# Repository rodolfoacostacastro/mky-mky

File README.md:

# A mky-mky clone for an RP2040 custom board

## Arduino Code

updated code after first workshop with minor improvements and better comments :)! 

This the code is situable for a makey makey that works with the chip RP2040.

To upload with the Arduino IDE, you will need to use this board definition(!):

https://github.com/earlephilhower/arduino-pico/releases/download/global/package_rp2040_index.json

go here --> Arduino >settings and scroll down until "Additional boards manager URLs" and paste the link above.

When selecting your board, asure you that it is the Raspberryi Pico/RP definition (and not the native from Arduino)

The code's been modified and works with the educational breakout-board created by Rodolfo Acosta Castro 
for the workshop "Into the Circuit" @ HfS, Berlin. October 2024

Credits:

 //////// MaKey MaKey FIRMWARE v1.4 /////////////
 by: Eric Rosenbaum, Jay Silver, and Jim Lindblom
 MIT Media Lab & Sparkfun
 release: 7/5/2012

## KiCad Files 

you find in this repository the KiCad Project files of the RP2040 Board and the Keyboard extension.
They were created using KiCad 8.0

## Fabrication Files

if you want to order the pcbs yourself you find all the needed files here

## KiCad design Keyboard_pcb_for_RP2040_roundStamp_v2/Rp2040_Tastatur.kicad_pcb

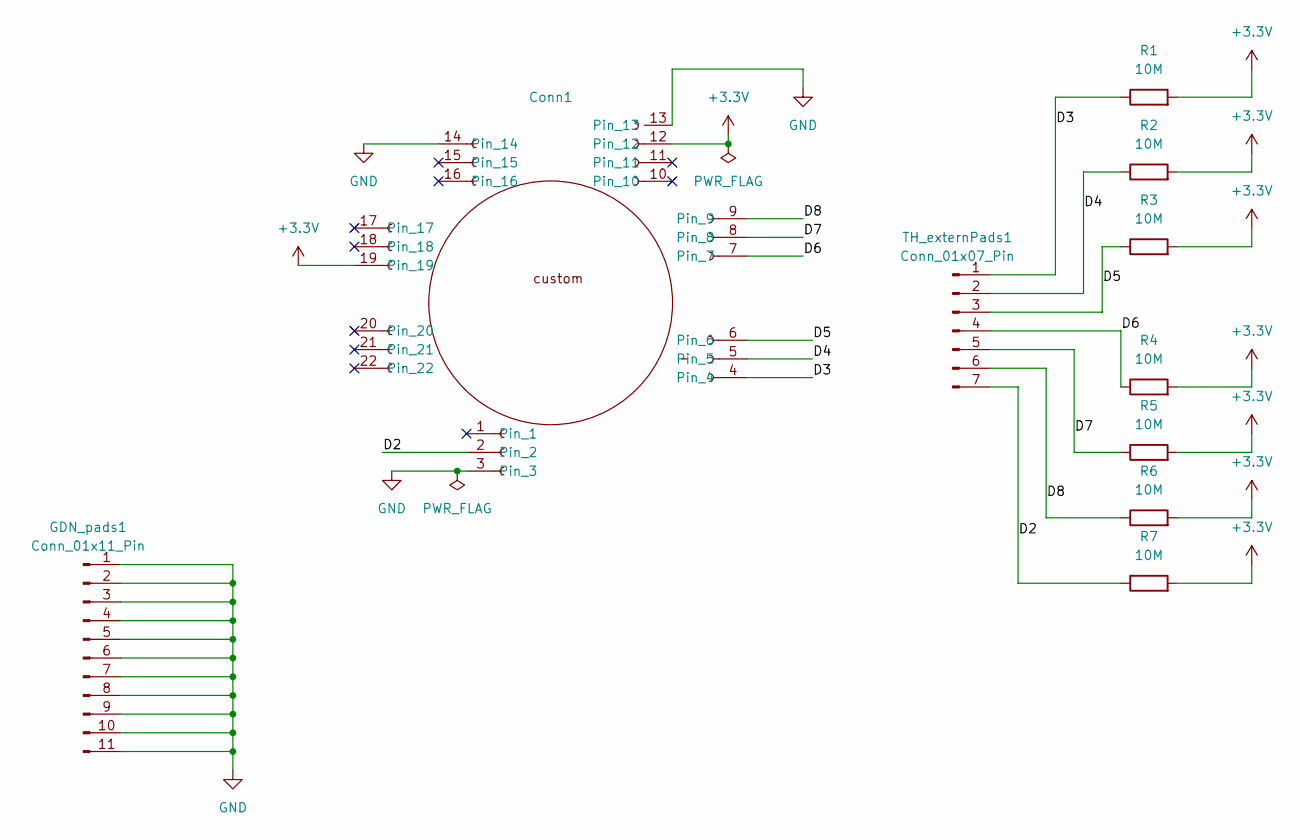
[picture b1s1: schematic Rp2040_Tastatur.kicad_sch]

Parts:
Conn1: mky_mky_boardPads
GDN_pads1: Conn_01x11_Pin; mky_mky_complete_GND
R1, R2, R3, R4, R5, R6, R7: 10M; R_0402_1005Metric_Pad0.72x0.64mm_HandSolder
TH_externPads1: Conn_01x07_Pin; mky_mky_externPads

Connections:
+3.3V: Conn1.12, Conn1.19, R1.2, R2.2, R3.2, R4.2, R5.2, R6.2, R7.2
/D2: Conn1.2, R7.1, TH_externPads1.7
/D3: Conn1.4, R1.1, TH_externPads1.1
/D4: Conn1.5, R2.1, TH_externPads1.2
/D5: Conn1.6, R3.1, TH_externPads1.3
/D6: Conn1.7, R4.1, TH_externPads1.4
/D7: Conn1.8, R5.1, TH_externPads1.5
/D8: Conn1.9, R6.1, TH_externPads1.6
GND: Conn1.3, Conn1.13, Conn1.14, GDN_pads1.1, GDN_pads1.2, GDN_pads1.3, GDN_pads1.4, GDN_pads1.5, GDN_pads1.6, GDN_pads1.7, GDN_pads1.8, GDN_pads1.9, GDN_pads1.10, GDN_pads1.11

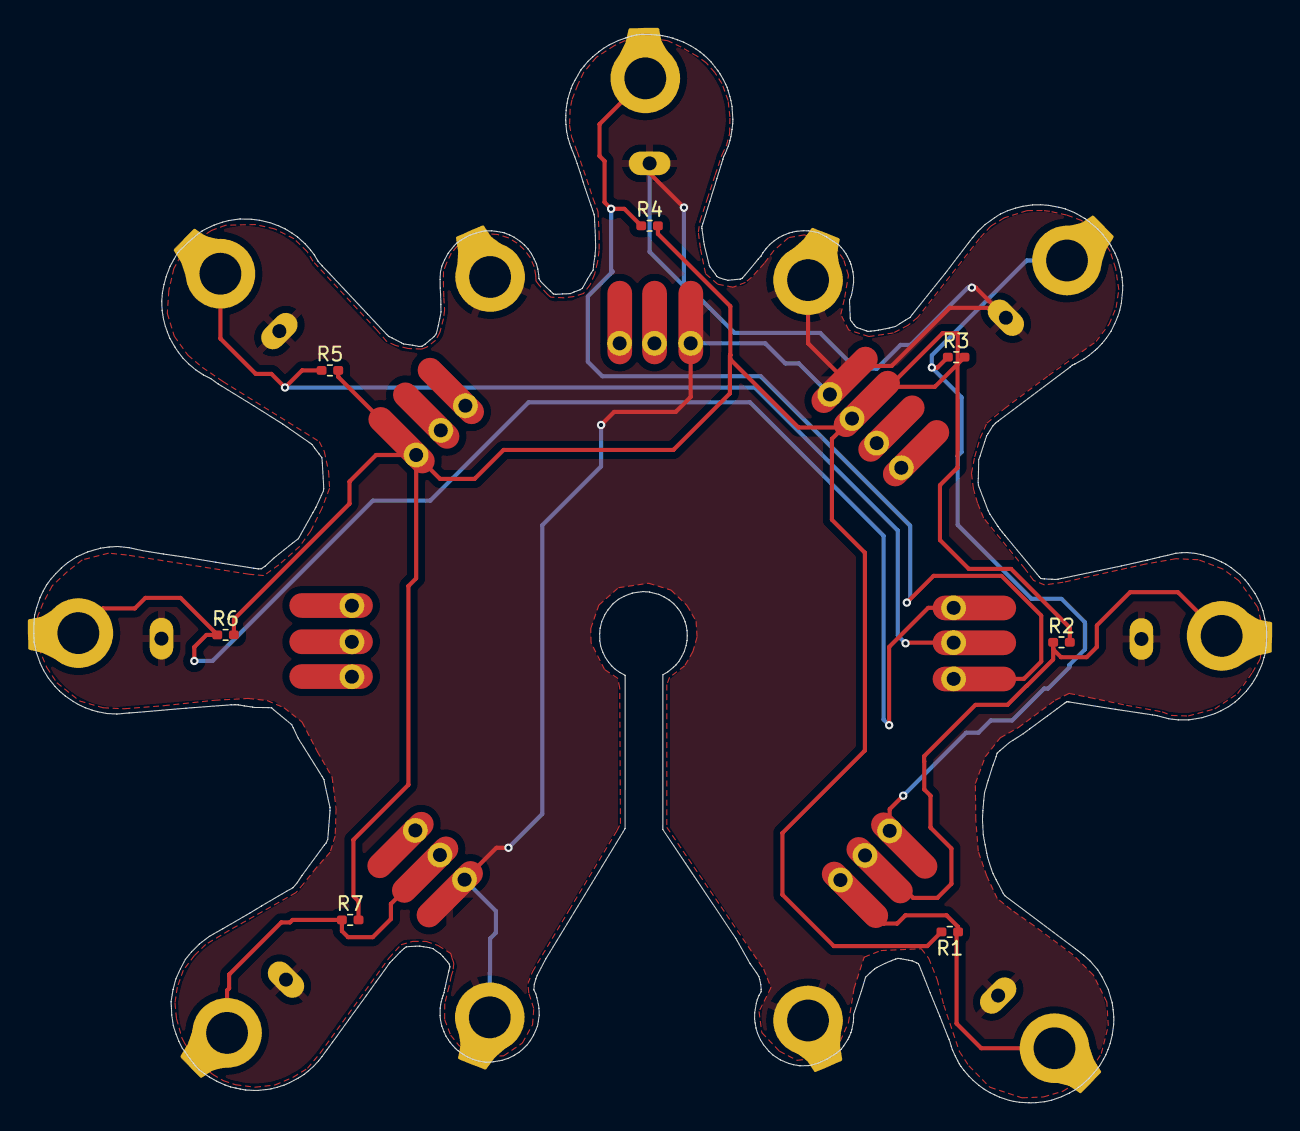
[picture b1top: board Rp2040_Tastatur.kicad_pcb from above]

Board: 2 copper layers, 88.5 x 76.7 mm, 10 parts (0 on the bottom side), 9 nets.

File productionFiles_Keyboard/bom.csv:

Designator,Footprint,Quantity,Value,LCSC Part #
Conn1,mky_mky_boardPads,1,~,
GDN_pads1,mky_mky_complete_GND,1,Conn_01x11_Pin,
"R1, R2, R3, R4, R5, R6, R7",0402,7,10M,
TH_externPads1,mky_mky_externPads,1,Conn_01x07_Pin,

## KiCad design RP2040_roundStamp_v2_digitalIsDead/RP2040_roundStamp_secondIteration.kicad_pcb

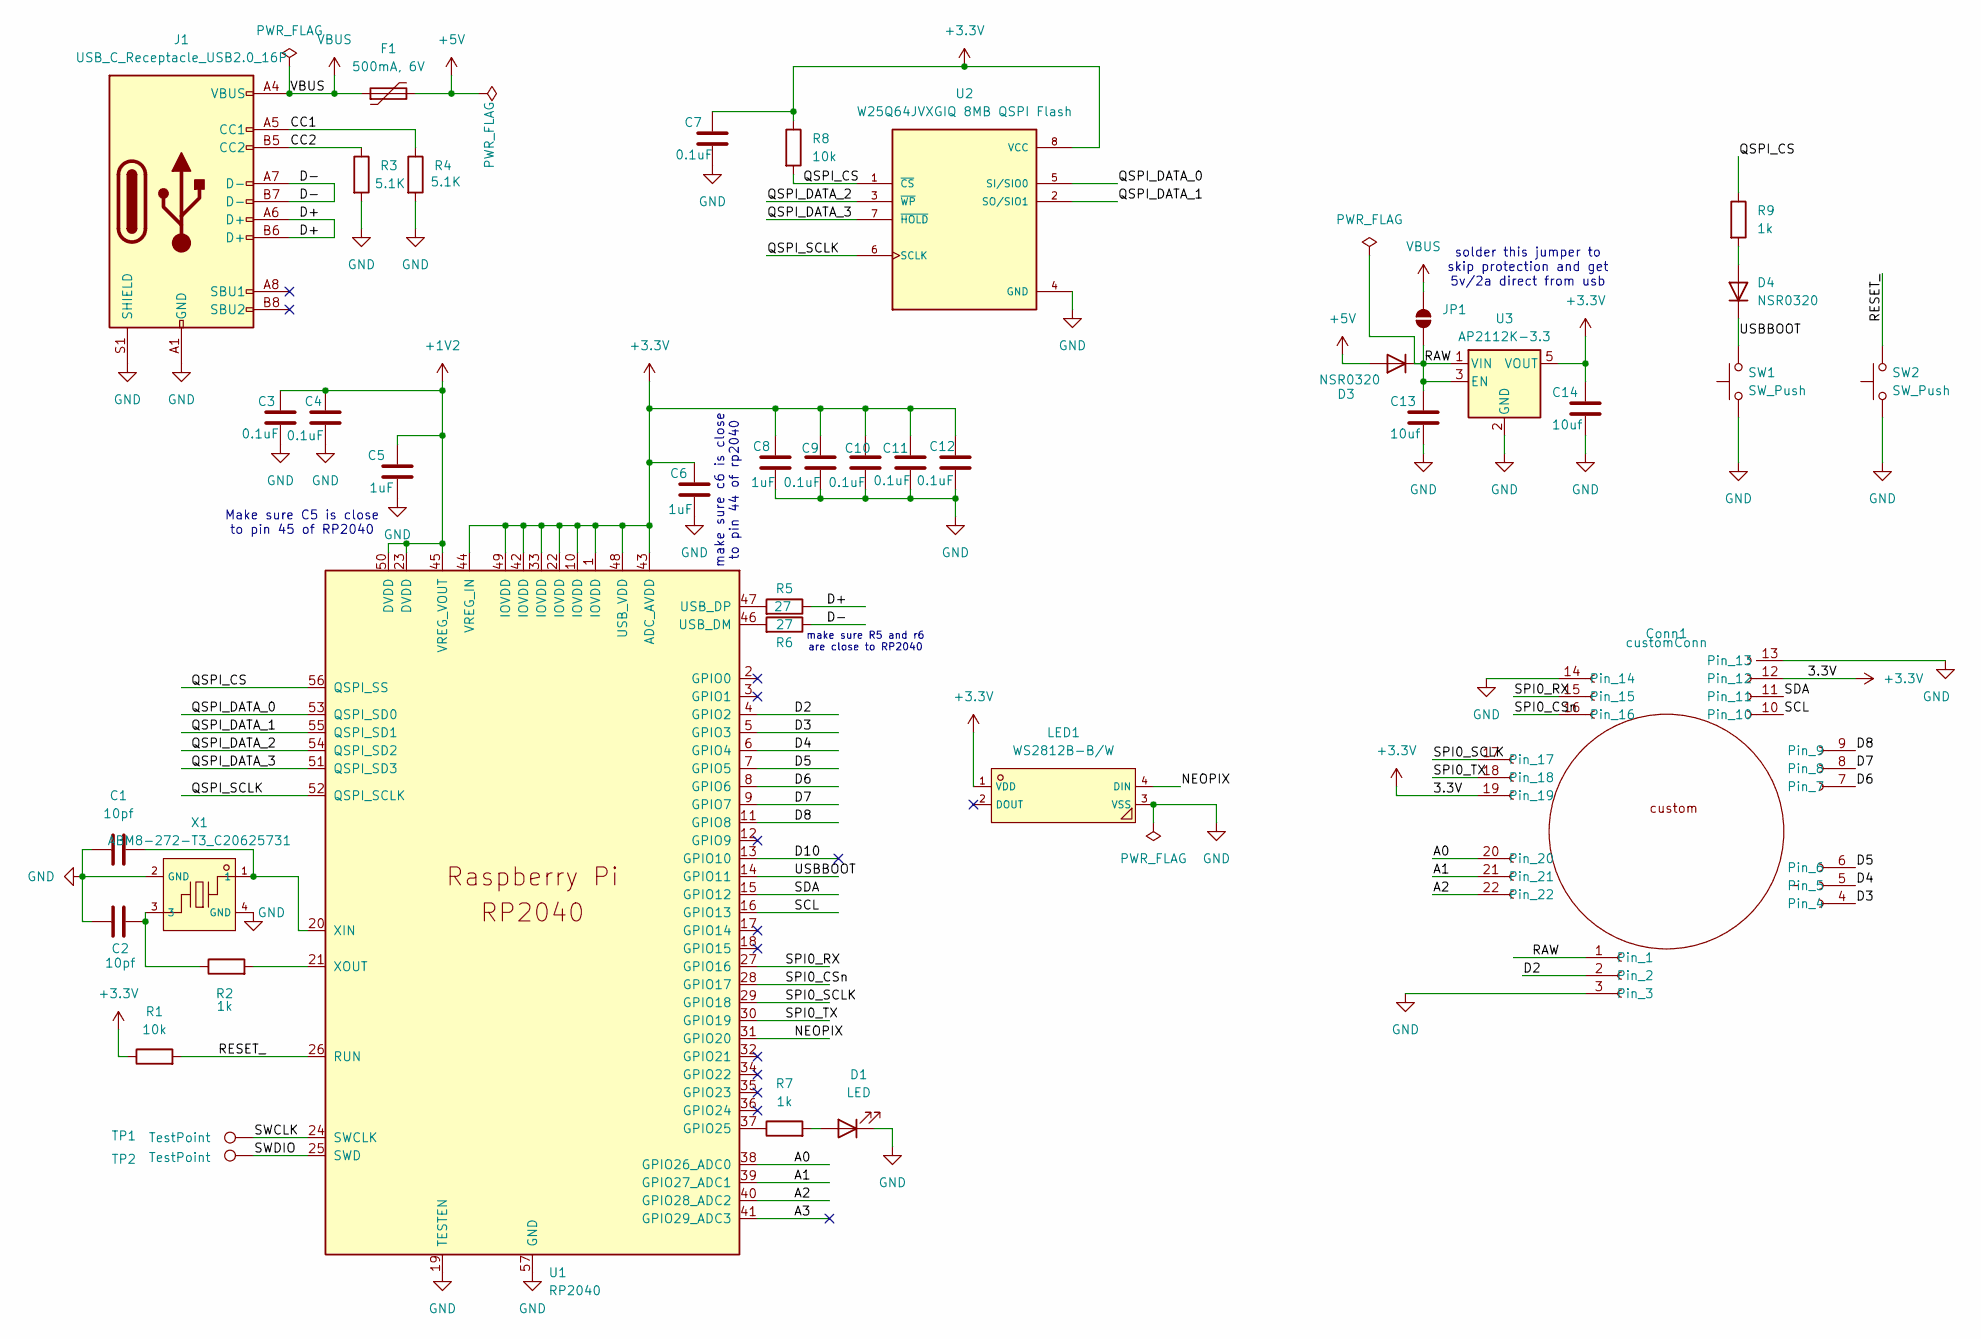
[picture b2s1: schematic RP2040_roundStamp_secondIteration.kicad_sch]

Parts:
C1, C2: 10pf; C_0603_1608Metric_Pad1.08x0.95mm_HandSolder; LCSC Part C1634
C3, C4, C7, C9, C10, C11, C12: 0.1uF; C_0603_1608Metric_Pad1.08x0.95mm_HandSolder; LCSC Part C14663
C5, C6, C8: 1uF; C_0603_1608Metric_Pad1.08x0.95mm_HandSolder; LCSC Part C15849
C13, C14: 10uf; C_0805_2012Metric_Pad1.18x1.45mm_HandSolder; LCSC Part C15850
Conn1: customConn; rp2040_roundStamp_BIG
D1: LED; LED_0603_1608Metric; LCSC Part C189306
D3, D4: NSR0320; D_SOD-323_HandSoldering; LCSC Part C48192
F1: 500mA, 6V; Fuse_0805_2012Metric; LCSC Part C269104
J1: USB_C_Receptacle_USB2.0_16P; USB_C_Receptacle_TYPE-C-31-M-12; LCSC Part C165948
JP1: SolderJumper_2_Open; SolderJumper-2_P1.3mm_Open_TrianglePad1.0x1.5mm
LED1: WS2812B-B/W; LED-SMD_4P-L5.0-W5.0-TL_WS2812B-B; LCSC C2761795
R1, R8: 10k; R_0603_1608Metric_Pad0.98x0.95mm_HandSolder; LCSC Part C25804
R2, R7, R9: 1k; R_0603_1608Metric_Pad0.98x0.95mm_HandSolder; LCSC Part C21190
R3, R4: 5.1K; R_0603_1608Metric_Pad0.98x0.95mm_HandSolder; LCSC Part C23186
R5, R6: 27; R_0603_1608Metric_Pad0.98x0.95mm_HandSolder; LCSC Part C100925
SW1, SW2: SW_Push; SW_B3U-1000P; LCSC Part C231329
TP1, TP2: TestPoint; TestPoint_Pad_D2.0mm
U1: RP2040; RP2040-QFN-56; LCSC Part C2040
U2: W25Q64JVXGIQ 8MB QSPI Flash; SON80P400X400X60-9N; LCSC Part C2940195
U3: AP2112K-3.3; SOT-23-5; LCSC Part C23380830
X1: ABM8-272-T3_C20625731; CRYSTAL-SMD_4P-L3.2-W2.5-BL; LCSC C20625731

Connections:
+1V2: C3.1, C4.1, C5.1, U1.23 (DVDD), U1.45 (VREG_VOUT), U1.50 (DVDD)
+3.3V: C6.1, C7.1, C8.1, C9.1, C10.1, C11.1, C12.1, C14.1, Conn1.12, Conn1.19, LED1.1 (VDD), R1.1, R8.1, U1.1 (IOVDD), U1.10 (IOVDD), U1.22 (IOVDD), U1.33 (IOVDD), U1.42 (IOVDD), U1.43 (ADC_AVDD), U1.44 (VREG_IN), U1.48 (USB_VDD), U1.49 (IOVDD), U2.8 (VCC), U3.5 (VOUT)
+5V: D3.2 (A), F1.2
/A0: Conn1.20, U1.38 (GPIO26_ADC0)
/A1: Conn1.21, U1.39 (GPIO27_ADC1)
/A2: Conn1.22, U1.40 (GPIO28_ADC2)
/A3: U1.41 (GPIO29_ADC3)
/CC1: J1.A5 (CC1), R4.1
/CC2: J1.B5 (CC2), R3.1
/D2: Conn1.2, U1.4 (GPIO2)
/D3: Conn1.4, U1.5 (GPIO3)
/D4: Conn1.5, U1.6 (GPIO4)
/D5: Conn1.6, U1.7 (GPIO5)
/D6: Conn1.7, U1.8 (GPIO6)
/D7: Conn1.8, U1.9 (GPIO7)
/D8: Conn1.9, U1.11 (GPIO8)
/D10: U1.13 (GPIO10)
/D+: J1.A6 (D+), J1.B6 (D+), R5.1
/D-: J1.A7 (D-), J1.B7 (D-), R6.1
/NEOPIX: LED1.4 (DIN), U1.31 (GPIO20)
/QSPI_CS: R8.2, R9.1, U1.56 (QSPI_SS), U2.1 (~CS)
/QSPI_DATA_0: U1.53 (QSPI_SD0), U2.5 (SI/SIO0)
/QSPI_DATA_1: U1.55 (QSPI_SD1), U2.2 (SO/SIO1)
/QSPI_DATA_2: U1.54 (QSPI_SD2), U2.3 (~WP)
/QSPI_DATA_3: U1.51 (QSPI_SD3), U2.7 (~HOLD)
/QSPI_SCLK: U1.52 (QSPI_SCLK), U2.6 (SCLK)
/RAW: C13.1, Conn1.1, D3.1 (K), JP1.1 (A), U3.1 (VIN), U3.3 (EN)
/RESET_: R1.2, SW2.2, U1.26 (RUN)
/SCL: Conn1.10, U1.16 (GPIO13)
/SDA: Conn1.11, U1.15 (GPIO12)
/SPI0_CSn: Conn1.16, U1.28 (GPIO17)
/SPI0_RX: Conn1.15, U1.27 (GPIO16)
/SPI0_SCLK: Conn1.17, U1.29 (GPIO18)
/SPI0_TX: Conn1.18, U1.30 (GPIO19)
/SWCLK: TP1.1, U1.24 (SWCLK)
/SWDIO: TP2.1, U1.25 (SWD)
/USBBOOT: D4.1 (K), SW1.2, U1.14 (GPIO11)
GND: C1.1, C2.1, C3.2, C4.2, C5.2, C6.2, C7.2, C8.2, C9.2, C10.2, C11.2, C12.2, C13.2, C14.2, Conn1.3, Conn1.13, Conn1.14, D1.1 (K), J1.A1 (GND), J1.A12 (GND), J1.B1 (GND), J1.B12 (GND), J1.S1 (SHIELD), LED1.3 (VSS), R3.2, R4.2, SW1.1, SW2.1, U1.19 (TESTEN), U1.57 (GND), U2.4 (GND), U3.2 (GND), X1.2 (GND), X1.4 (GND)
unnamed: C2.2, R2.1, X1.3
unnamed: D1.2 (A), R7.2
unnamed: D4.2 (A), R9.2
unnamed: R7.1, U1.37 (GPIO25)
unnamed: R6.2, U1.46 (USB_DM)
unnamed: R5.2, U1.47 (USB_DP)
unnamed: C1.2, U1.20 (XIN), X1.1
unnamed: R2.2, U1.21 (XOUT)
VBUS: F1.1, J1.A4 (VBUS), J1.A9 (VBUS), J1.B4 (VBUS), J1.B9 (VBUS), JP1.2

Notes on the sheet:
make sure R5 and r6 are close to RP2040
make sure c6 is close to pin 44 of rp2040
Make sure C5 is close to pin 45 of RP2040
solder this jumper to skip protection and get 5v/2a direct from usb

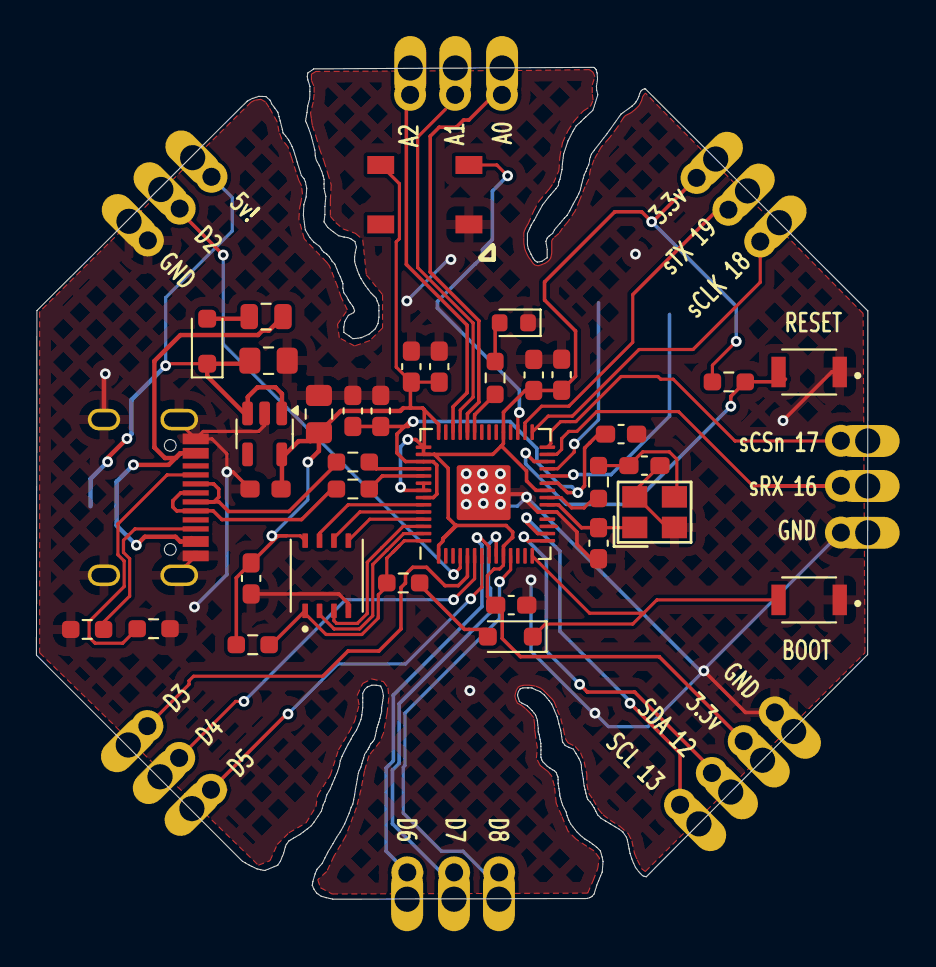
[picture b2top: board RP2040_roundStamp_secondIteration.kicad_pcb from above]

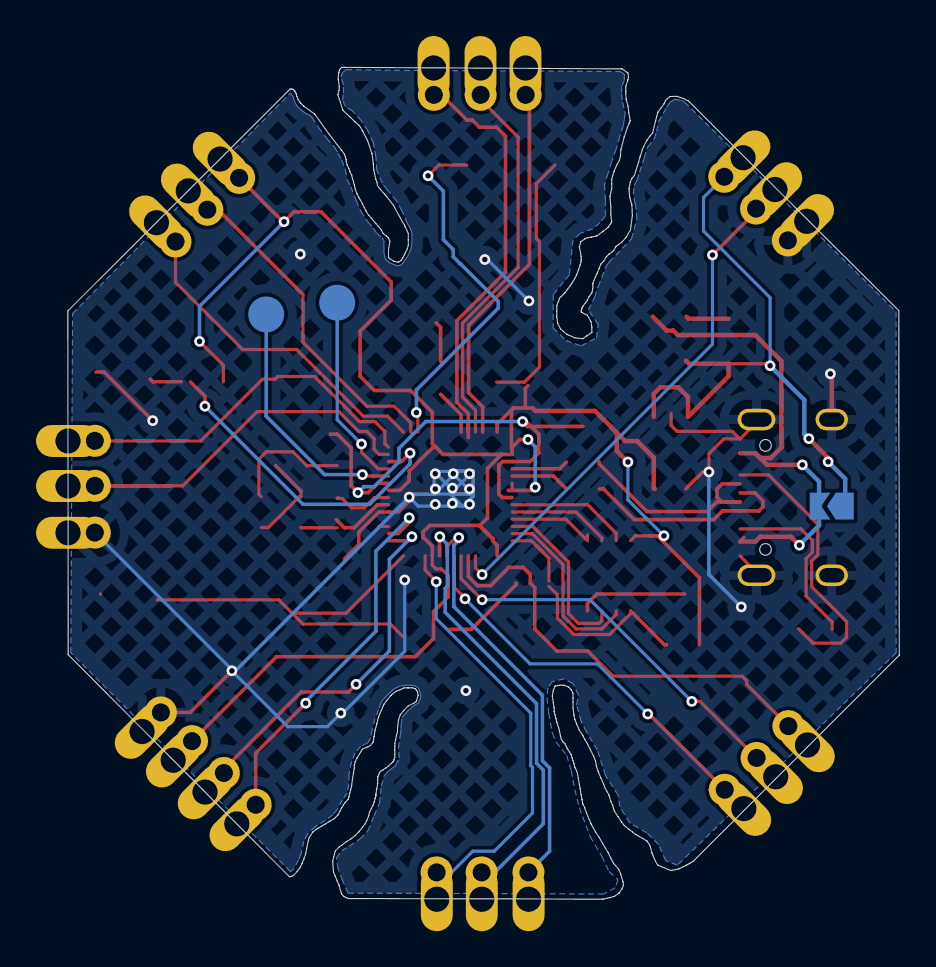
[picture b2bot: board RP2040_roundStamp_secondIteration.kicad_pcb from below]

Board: 2 copper layers, 46.2 x 46.2 mm, 39 parts (3 on the bottom side), 45 nets.

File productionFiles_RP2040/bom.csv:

Designator,Footprint,Quantity,Value,LCSC Part #
"C1, C2",0603,2,10pf,C1634
"C10, C11, C12, C3, C4, C7, C9",0603,7,0.1uF,C14663
"C13, C14",0805,2,10uf,C15850
"C5, C6, C8",0603,3,1uF,C15849
Conn1,rp2040_roundStamp_BIG,1,customConn,
D1,0603,1,LED,C189306
"D3, D4",D_SOD-323_HandSoldering,2,NSR0320,C48192
F1,0805,1,"500mA, 6V",C269104
J1,USB_C_Receptacle_TYPE-C-31-M-12,1,USB_C_Receptacle_USB2.0_16P,C165948
LED1,LED-SMD_4P-L5.0-W5.0-TL_WS2812B-B,1,WS2812B-B/W,C2761795
"R1, R8",0603,2,10k,C25804
"R2, R7, R9",0603,3,1k,C21190
"R3, R4",0603,2,5.1K,C23186
"R5, R6",0603,2,27,C100925
"SW1, SW2",SW_B3U-1000P,2,SW_Push,C231329
"TP1, TP2",TestPoint_Pad_D2.0mm,2,TestPoint,
U1,RP2040-QFN-56,1,RP2040,C2040
U2,SON80P400X400X60-9N,1,W25Q64JVXGIQ 8MB QSPI Flash,C2940195
U3,SOT-23-5,1,AP2112K-3.3,C23380830
X1,CRYSTAL-SMD_4P-L3.2-W2.5-BL,1,ABM8-272-T3_C20625731,C20625731

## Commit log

2024-10-23 Update README.md
    tip fehler
2024-10-23 Update README.md
    updated readme with credits
2024-10-24 Update mky-mky.ino
    code description updated
2024-10-31 Delete RP2040_roundStamp_v2_digitalIsDead directory
    take out unnecessary folders
2024-10-31 Delete mky-mky directory
    borrar codigo viejo
2024-10-31 Update README.md
    updated description of the code
2024-10-31 Update README.md
    details about kicad
2024-10-31 Delete Keyboard_pcb_for_RP2040_roundStamp_v2 directory
    borrando por tener nombre confuso 1
2024-10-31 Delete RP2040_roundStamp_v2_digitalIsDead directory
    borrando por tener nombre confuso 2
2024-10-31 Update README.md
    updated description
